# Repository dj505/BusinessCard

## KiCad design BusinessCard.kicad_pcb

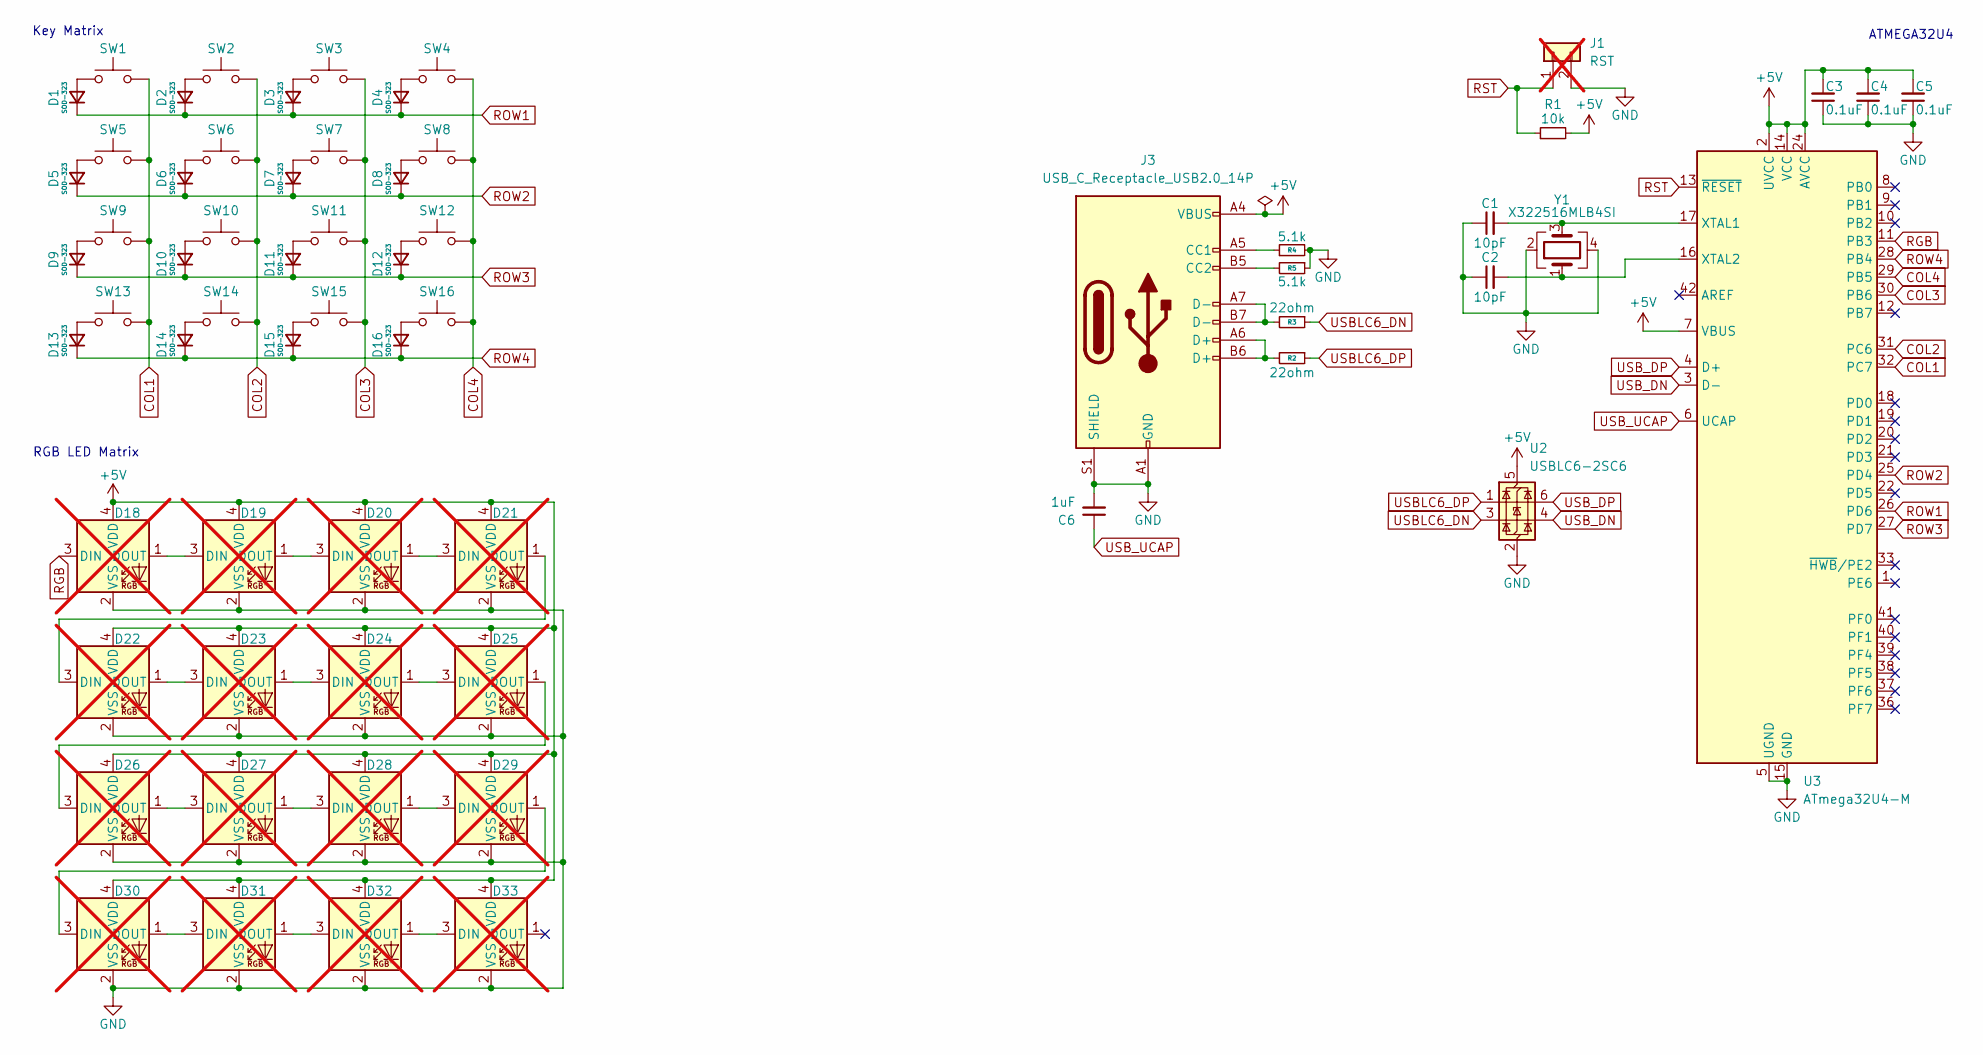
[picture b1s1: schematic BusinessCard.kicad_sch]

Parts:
C1, C2: 10pF; C_0402_1005Metric; LCSC C32949
C3, C4, C5: 0.1uF; C_0402_1005Metric; LCSC C1525
C6: 1uF; C_0603_1608Metric; LCSC C15849
D1, D2, D3, D4, D5, D6, D7, D8, D9, D10, D11, D12, D13, D14, D15, D16: SOD-323; D_SOD-323; LCSC C2128
D18, D19, D20, D21, D22, D23, D24, D25, D26, D27, D28, D29, D30, D31, D32, D33: WS2812B-2020; LED_WS2812B-2020_PLCC4_2.0x2.0mm; LCSC C965555; not fitted
J1: RST; PinHeader_1x02_P1.27mm_Vertical; not fitted
J3: USB_C_Receptacle_USB2.0_14P; USB_C_Receptacle_G-Switch_GT-USB-7010ASV; LCSC C393939
R1: 10k; R_0402_1005Metric; LCSC C25744
R2, R3: 22ohm; R_0402_1005Metric; LCSC C25092
R4, R5: 5.1k; R_0402_1005Metric; LCSC C25905
SW1, SW2, SW3, SW4, SW5, SW6, SW7, SW8, SW9, SW10, SW11, SW12, SW13, SW14, SW15, SW16: SW_Push; SW_Push_1P1T_XKB_TS-1187A; LCSC C318884
U2: USBLC6-2SC6; SOT-23-6; LCSC C2827654
U3: ATmega32U4-M; QFN-44-1EP_7x7mm_P0.5mm_EP5.2x5.2mm; LCSC C112161
Y1: X322516MLB4SI; Crystal_SMD_3225-4Pin_3.2x2.5mm; LCSC C13738

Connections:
+5V: C3.2, C4.2, C5.2, D18.4 (VDD), D19.4 (VDD), D20.4 (VDD), D21.4 (VDD), D22.4 (VDD), D23.4 (VDD), D24.4 (VDD), D25.4 (VDD), D26.4 (VDD), D27.4 (VDD), D28.4 (VDD), D29.4 (VDD), D30.4 (VDD), D31.4 (VDD), D32.4 (VDD), D33.4 (VDD), J3.A4 (VBUS), J3.A9 (VBUS), J3.B4 (VBUS), J3.B9 (VBUS), R1.2, U2.5 (VBUS), U3.2 (UVCC), U3.7 (VBUS), U3.14 (VCC), U3.24 (AVCC), U3.34 (VCC), U3.44 (AVCC)
COL1: SW1.2, SW5.2, SW9.2, SW13.2, U3.32 (PC7)
COL2: SW2.2, SW6.2, SW10.2, SW14.2, U3.31 (PC6)
COL3: SW3.2, SW7.2, SW11.2, SW15.2, U3.30 (PB6)
COL4: SW4.2, SW8.2, SW12.2, SW16.2, U3.29 (PB5)
GND: C1.1, C2.1, C3.1, C4.1, C5.1, C6.2, D18.2 (VSS), D19.2 (VSS), D20.2 (VSS), D21.2 (VSS), D22.2 (VSS), D23.2 (VSS), D24.2 (VSS), D25.2 (VSS), D26.2 (VSS), D27.2 (VSS), D28.2 (VSS), D29.2 (VSS), D30.2 (VSS), D31.2 (VSS), D32.2 (VSS), D33.2 (VSS), J1.2, J3.A1 (GND), J3.A12 (GND), J3.B1 (GND), J3.B12 (GND), J3.S1 (SHIELD), R4.2, R5.1, U2.2 (GND), U3.5 (UGND), U3.15 (GND), U3.23 (GND), U3.35 (GND), U3.43 (GND), U3.45 (GND), Y1.2, Y1.4
unnamed: D1.2 (A), SW1.1
unnamed: D2.2 (A), SW2.1
unnamed: D3.2 (A), SW3.1
unnamed: D4.2 (A), SW4.1
unnamed: D5.2 (A), SW5.1
unnamed: D6.2 (A), SW6.1
unnamed: D7.2 (A), SW7.1
unnamed: D8.2 (A), SW8.1
unnamed: D9.2 (A), SW9.1
unnamed: D10.2 (A), SW10.1
unnamed: D11.2 (A), SW11.1
unnamed: D12.2 (A), SW12.1
unnamed: D13.2 (A), SW13.1
unnamed: D14.2 (A), SW14.1
unnamed: D15.2 (A), SW15.1
unnamed: D16.2 (A), SW16.1
unnamed: D18.1 (DOUT), D19.3 (DIN)
unnamed: D19.1 (DOUT), D20.3 (DIN)
unnamed: D20.1 (DOUT), D21.3 (DIN)
unnamed: D21.1 (DOUT), D22.3 (DIN)
unnamed: D22.1 (DOUT), D23.3 (DIN)
unnamed: D23.1 (DOUT), D24.3 (DIN)
unnamed: D24.1 (DOUT), D25.3 (DIN)
unnamed: D25.1 (DOUT), D26.3 (DIN)
unnamed: D26.1 (DOUT), D27.3 (DIN)
unnamed: D27.1 (DOUT), D28.3 (DIN)
unnamed: D28.1 (DOUT), D29.3 (DIN)
unnamed: D29.1 (DOUT), D30.3 (DIN)
unnamed: D30.1 (DOUT), D31.3 (DIN)
unnamed: D31.1 (DOUT), D32.3 (DIN)
unnamed: D32.1 (DOUT), D33.3 (DIN)
unnamed: J3.A5 (CC1), R4.1
unnamed: J3.B5 (CC2), R5.2
unnamed: J3.A6 (D+), J3.B6 (D+), R2.2
unnamed: J3.A7 (D-), J3.B7 (D-), R3.2
unnamed: C1.2, U3.17 (XTAL1), Y1.3
unnamed: C2.2, U3.16 (XTAL2), Y1.1
RGB: D18.3 (DIN), U3.11 (PB3)
ROW1: D1.1 (K), D2.1 (K), D3.1 (K), D4.1 (K), U3.26 (PD6)
ROW2: D5.1 (K), D6.1 (K), D7.1 (K), D8.1 (K), U3.25 (PD4)
ROW3: D9.1 (K), D10.1 (K), D11.1 (K), D12.1 (K), U3.27 (PD7)
ROW4: D13.1 (K), D14.1 (K), D15.1 (K), D16.1 (K), U3.28 (PB4)
RST: J1.1, R1.1, U3.13 (~RESET)
USBLC6_DN: R3.1, U2.3 (I/O2)
USBLC6_DP: R2.1, U2.1 (I/O1)
USB_DN: U2.4 (I/O2), U3.3 (D-)
USB_DP: U2.6 (I/O1), U3.4 (D+)
USB_UCAP: C6.1, U3.6 (UCAP)

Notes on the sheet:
RGB LED Matrix
ATMEGA32U4
Key Matrix

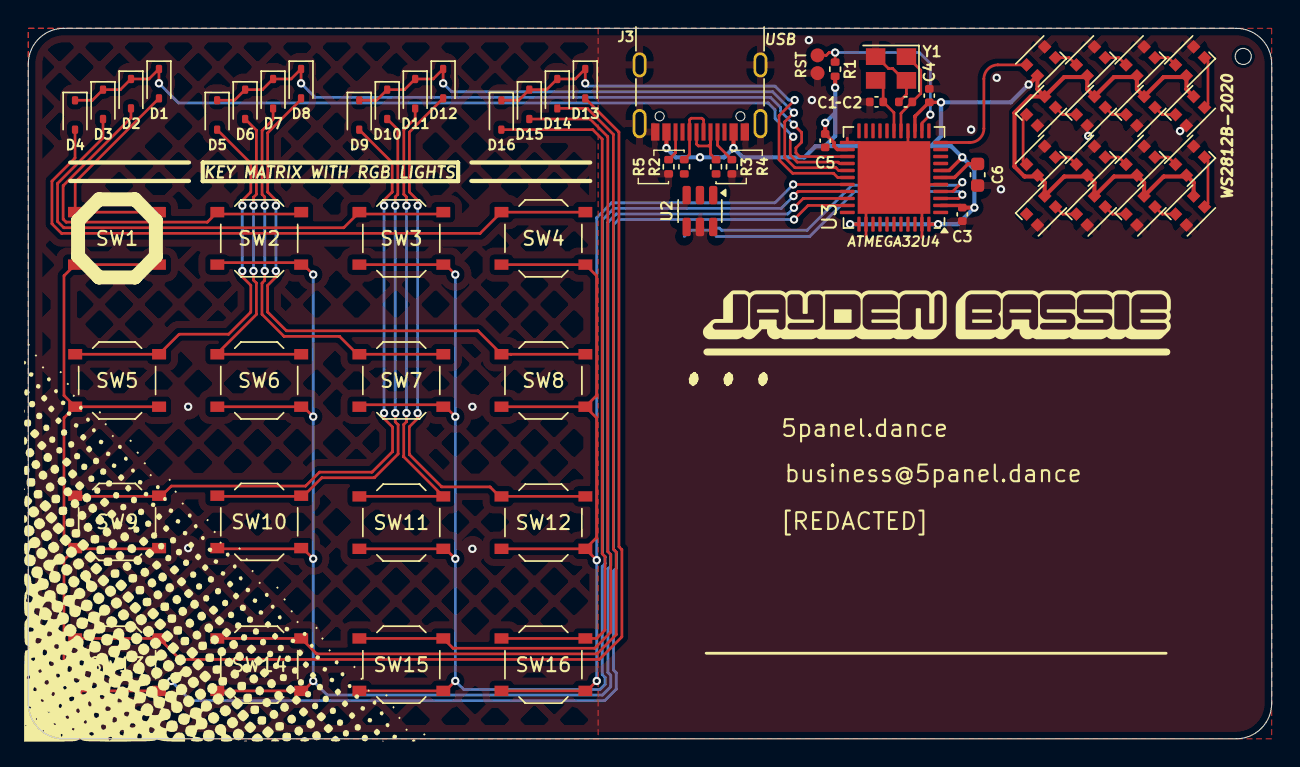
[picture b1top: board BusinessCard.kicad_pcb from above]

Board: 2 copper layers, 88.9 x 50.8 mm, 64 parts (0 on the bottom side), 54 nets.

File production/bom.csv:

Designator,Footprint,Quantity,Value,LCSC Part #
"C1, C2",0402,2,10pF,C32949
"C3, C4, C5",0402,3,0.1uF,C1525
C6,0603,1,1uF,C15849
"D1, D10, D11, D12, D13, D14, D15, D16, D2, D3, D4, D5, D6, D7, D8, D9",D_SOD-323,16,SOD-323,C2128
"D18, D19, D20, D21, D22, D23, D24, D25, D26, D27, D28, D29, D30, D31, D32, D33",LED_WS2812B-2020_PLCC4_2.0x2.0mm,16,WS2812B-2020,C965555
J1,PinHeader_1x02_P1.27mm_Vertical,1,RST,
J3,USB_C_Receptacle_G-Switch_GT-USB-7010ASV,1,USB_C_Receptacle_USB2.0_14P,
R1,0402,1,10k,C25744
"R2, R3",0402,2,22ohm,C25092
"R4, R5",0402,2,5.1k,C25905
"SW1, SW10, SW11, SW12, SW13, SW14, SW15, SW16, SW2, SW3, SW4, SW5, SW6, SW7, SW8, SW9",SW_Push_1P1T_XKB_TS-1187A,16,SW_Push,C318884
U2,SOT-23-6,1,USBLC6-2SC6,C2827654
U3,QFN-44-1EP_7x7mm_P0.5mm_EP5.2x5.2mm,1,ATmega32U4-M,C112161
Y1,Crystal_SMD_3225-4Pin_3.2x2.5mm,1,X322516MLB4SI,C13738

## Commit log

2024-06-29 Add QR code with wiki link
2024-06-29 Placeholder 3D models
2024-06-29 Abusing QR code error correction
2024-07-01 Visual changes, alignment fixes, other tweaks
2024-07-02 More tweaking, text changes and adjustments
2024-11-19 Updated to the current revision
2024-11-21 add gh-pages directory
2024-11-21 apparently it has to be called "docs"
2024-11-22 Update docs
2024-11-26 Fix viewport stuff in docs
2024-11-26 oops
2024-12-01 docs update

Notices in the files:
BusinessCard.kicad_pcb:
Link icon by SimpleIcon (http://www.simpleicon.com/) via Wikimedia Commons
https://creativecommons.org/licenses/by/3.0
